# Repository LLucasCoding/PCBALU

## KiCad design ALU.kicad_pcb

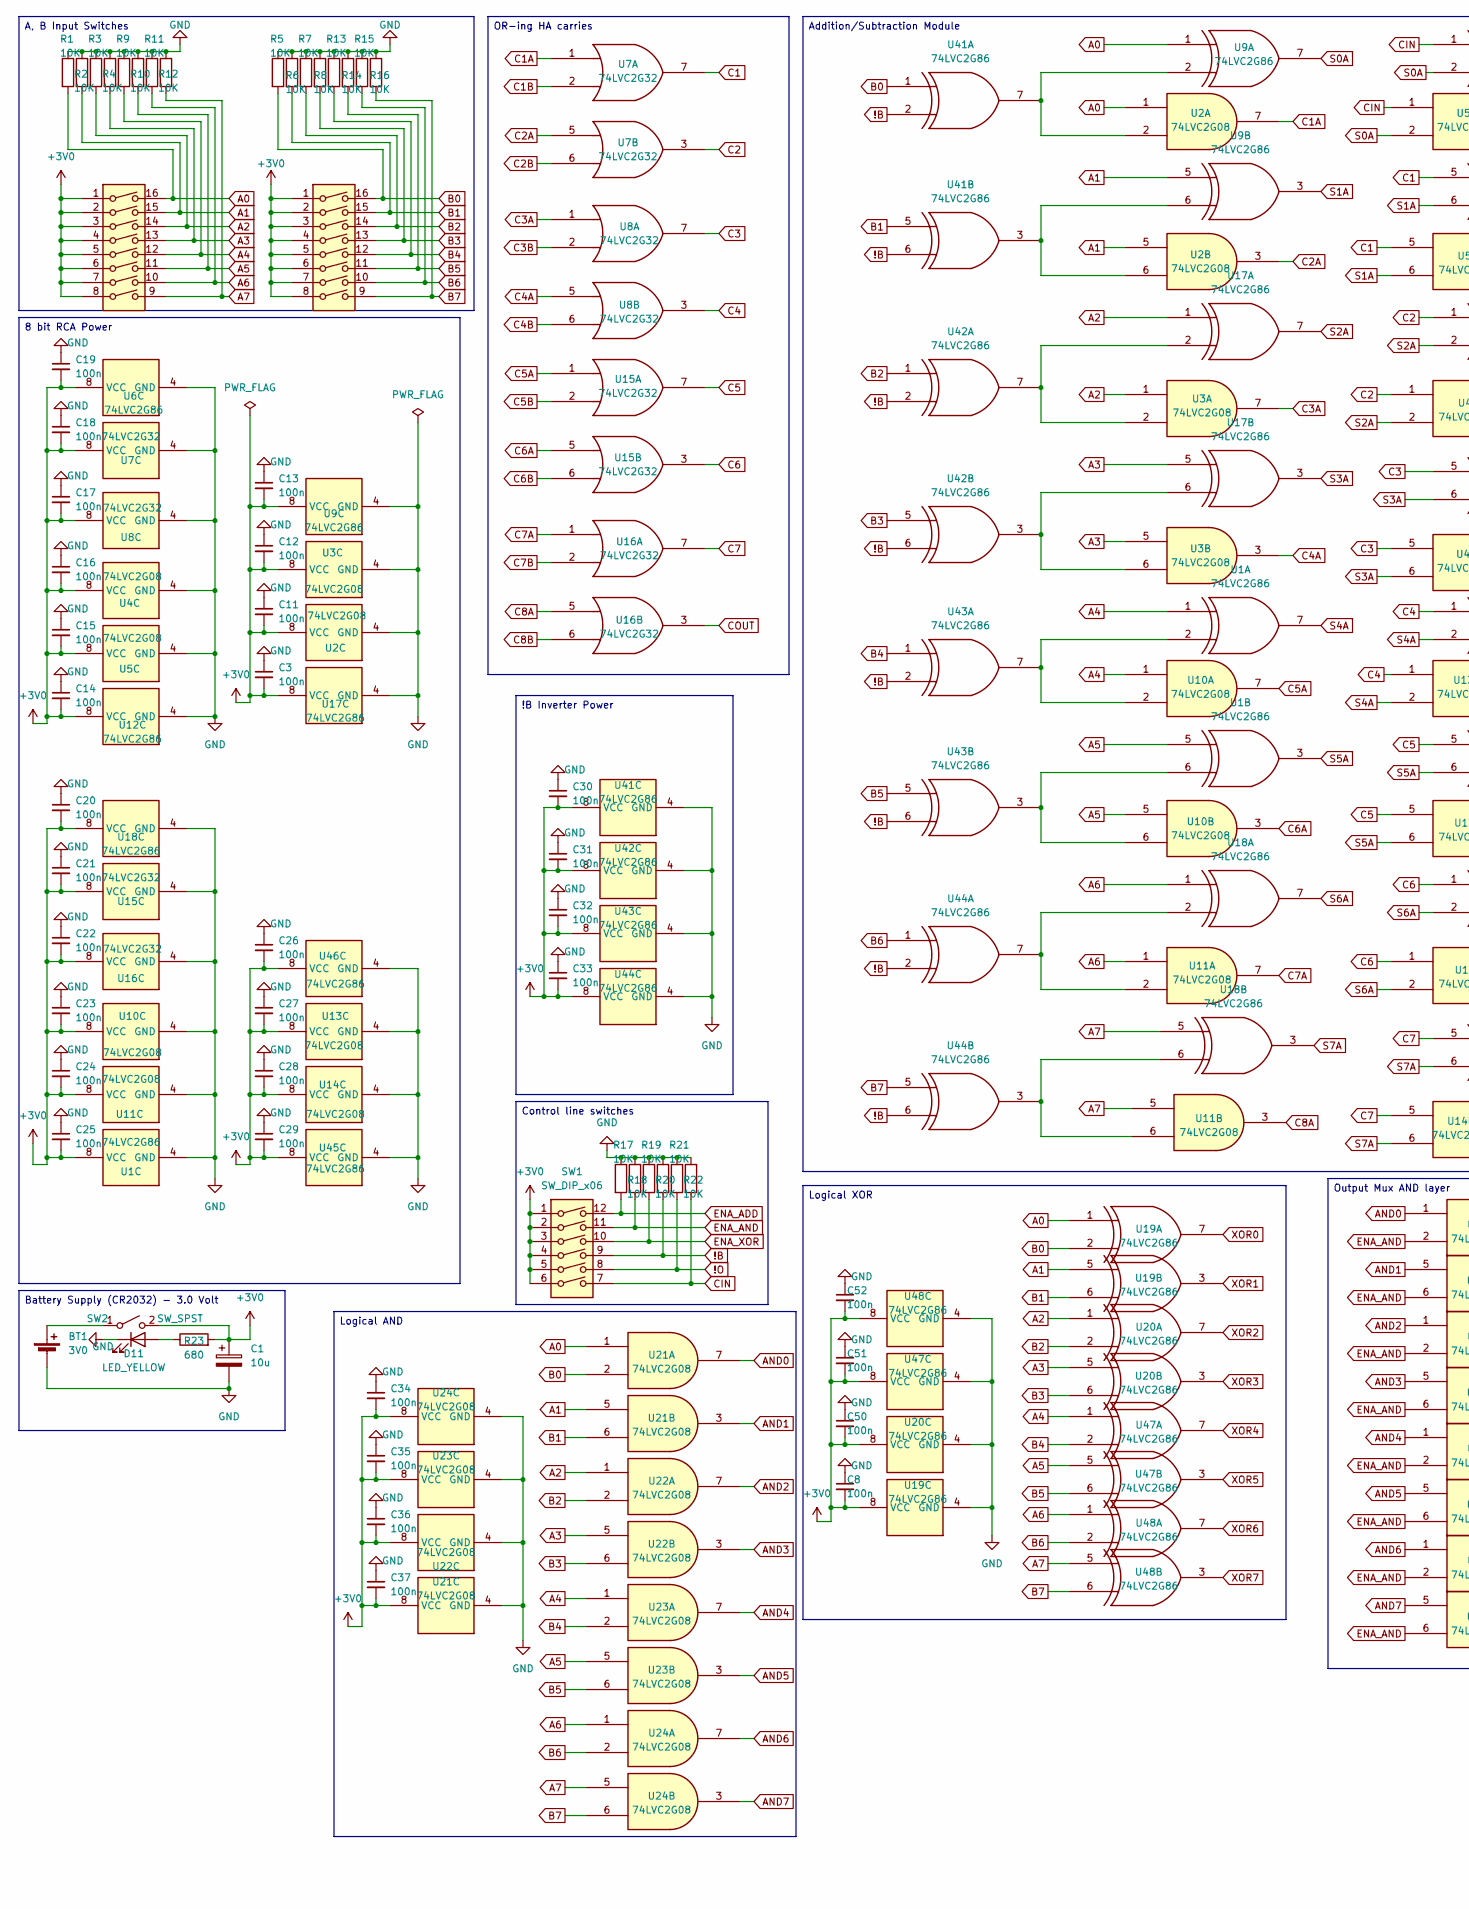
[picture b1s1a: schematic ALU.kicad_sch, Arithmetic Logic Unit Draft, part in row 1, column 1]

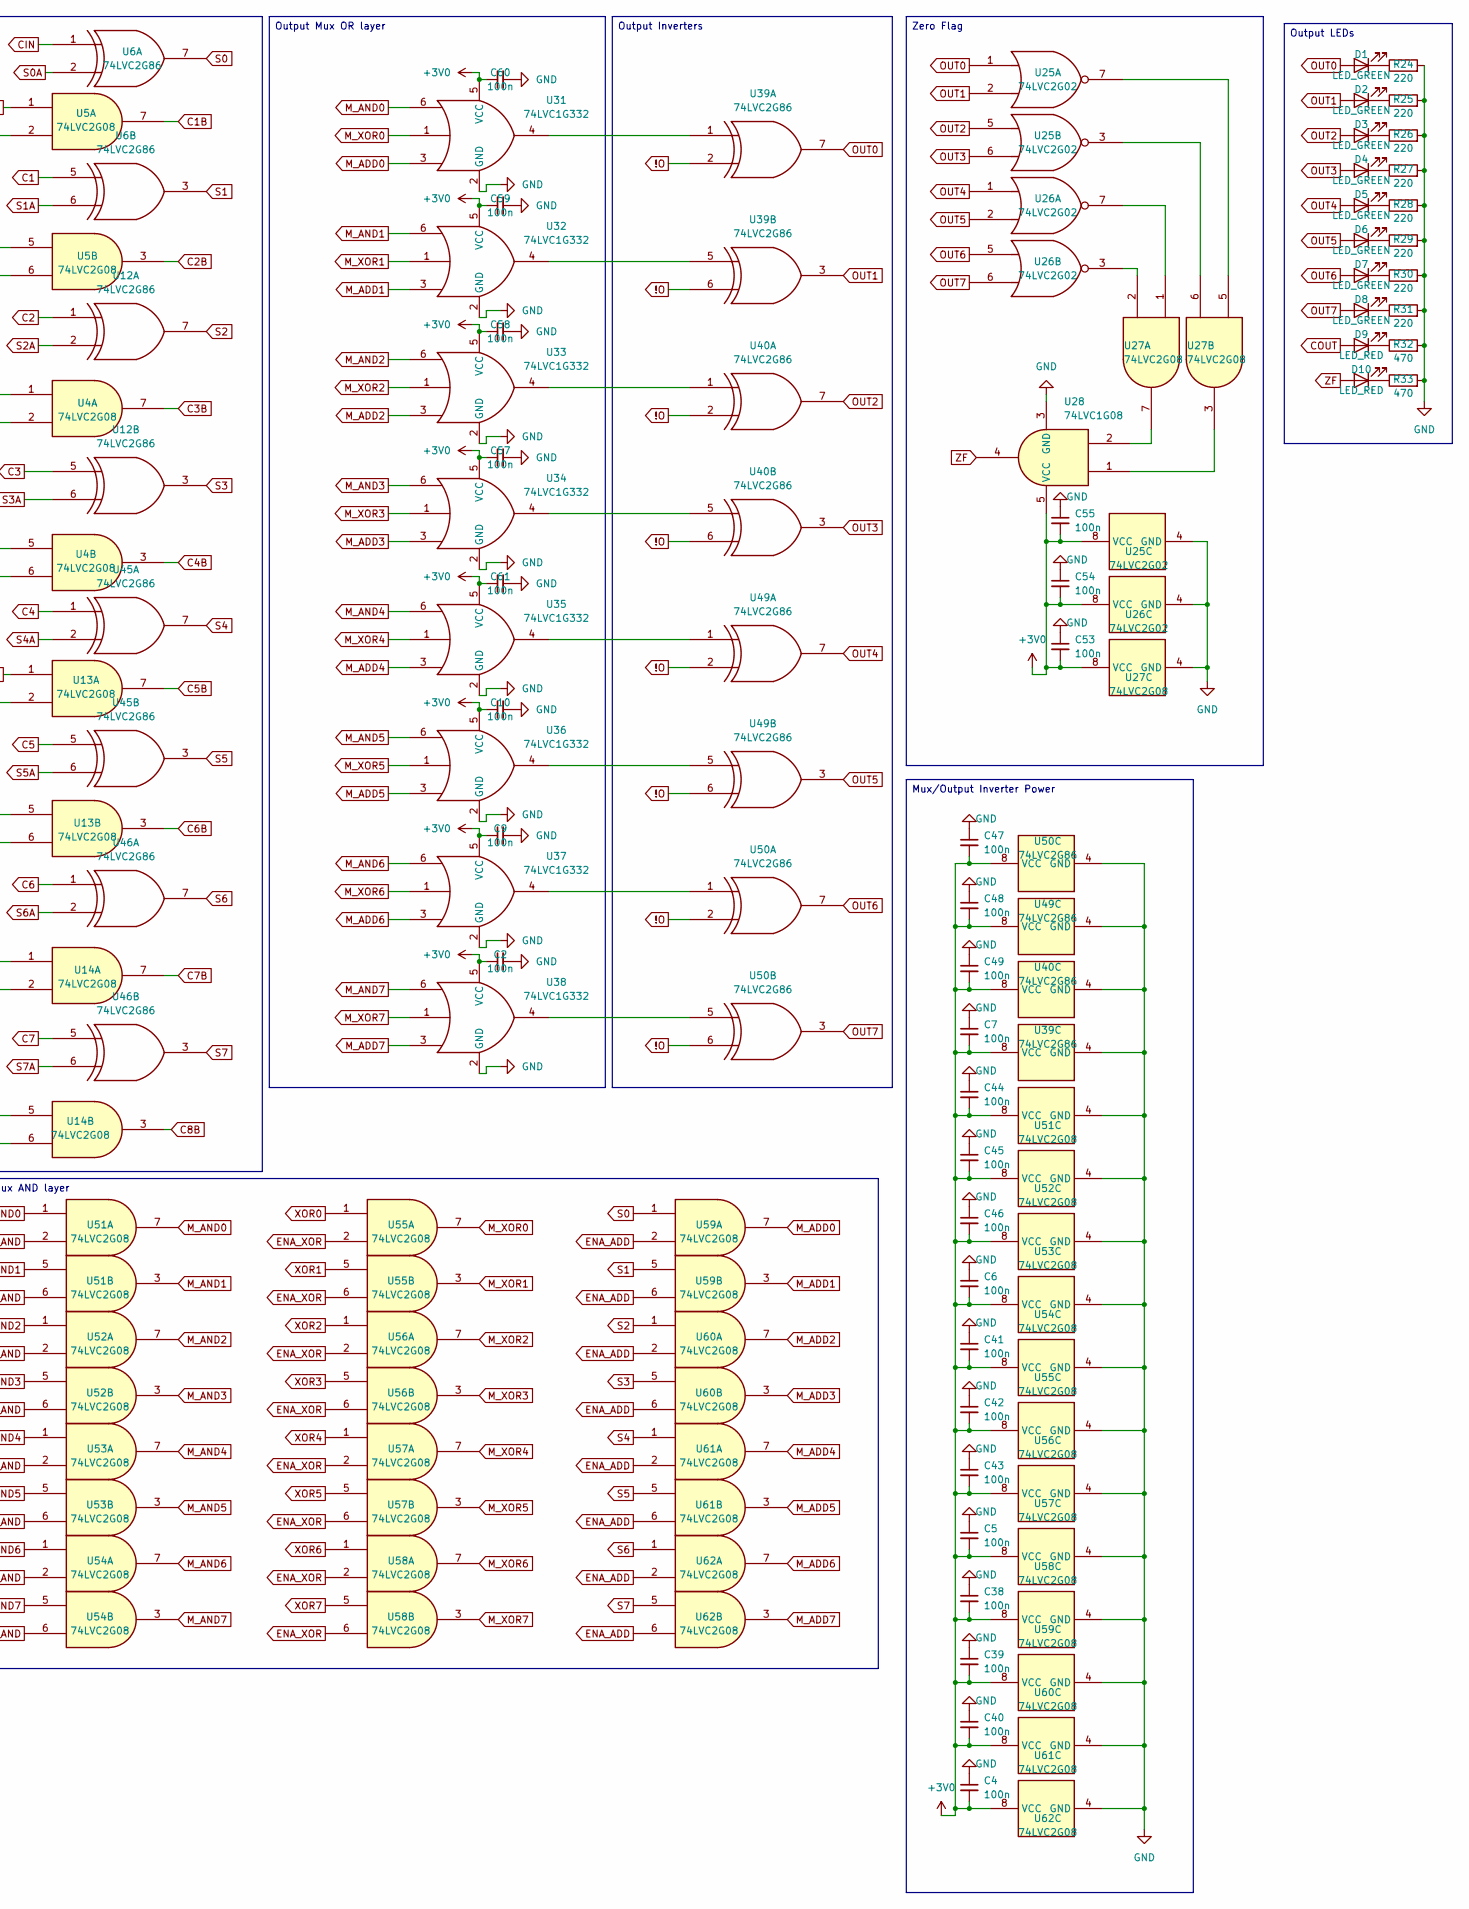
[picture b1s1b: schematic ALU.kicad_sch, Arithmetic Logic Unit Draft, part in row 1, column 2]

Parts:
BT1: 3V0; Battery_Panasonic_CR2032-VS1N_Vertical_CircularHoles
C1: 10u; CP_Radial_D5.0mm_P2.00mm
C2, C3, C4, C5, C6, C7, C8, C9, C10, C11, C12, C13, C14, C15, C16, C17, C18, C19, C20, C21, C22, C23, C24, C25, C26, C27, C28, C29, C30, C31, C32, C33, C34, C35, C36, C37, C38, C39, C40, C41, C42, C43, C44, C45, C46, C47, C48, C49, C50, C51, C52, C53, C54, C55, C57, C58, C59, C60, C61: 100n; C_0805_2012Metric
D1, D2, D3, D4, D5, D6, D7, D8: LED_GREEN; LED_0805_2012Metric
D9, D10: LED_RED; LED_0805_2012Metric
D11: LED_YELLOW; LED_0603_1608Metric
R1, R2, R3, R4, R5, R6, R7, R8, R9, R10, R11, R12, R13, R14, R15, R16, R17, R18, R19, R20, R21, R22: 10K; R_0805_2012Metric
R23: 680; R_0805_2012Metric
R24, R25, R26, R27, R28, R29, R30, R31: 220; R_0805_2012Metric
R32, R33: 470; R_0805_2012Metric
SW1: SW_DIP_x06; SW_DIP_SPSTx06_Slide_9.78x17.42mm_W7.62mm_P2.54mm
SW2: SW_SPST; SW_DIP_SPSTx01_Slide_9.78x4.72mm_W7.62mm_P2.54mm
SW3, SW4: SW_DIP_x08; SW_DIP_SPSTx08_Slide_9.78x22.5mm_W7.62mm_P2.54mm
U1, U6, U9, U12, U17, U18, U19, U20, U39, U40, U41, U42, U43, U44, U45, U46, U47, U48, U49, U50: 74LVC2G86; VSSOP-8_2.3x2mm_P0.5mm
U2, U3, U4, U5, U10, U11, U13, U14, U21, U22, U23, U24, U27, U51, U52, U53, U54, U55, U56, U57, U58, U59, U60, U61, U62: 74LVC2G08; VSSOP-8_2.3x2mm_P0.5mm
U7, U8, U15, U16: 74LVC2G32; VSSOP-8_2.3x2mm_P0.5mm
U25, U26: 74LVC2G02; VSSOP-8_2.3x2mm_P0.5mm
U28: 74LVC1G08; SOT-23-5
U31, U32, U33, U34, U35, U36, U37, U38: 74LVC1G332; SOT-23-6

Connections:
!B: R20.2, SW1.9, U41.2, U41.6, U42.2, U42.6, U43.2, U43.6, U44.2, U44.6
!O: R21.2, SW1.8, U39.2, U39.6, U40.2, U40.6, U49.2, U49.6, U50.2, U50.6
+3V0: C1.1, C2.1, C3.2, C4.2, C5.2, C6.2, C7.2, C8.2, C9.1, C10.1, C11.2, C12.2, C13.2, C14.2, C15.2, C16.2, C17.2, C18.2, C19.2, C20.2, C21.2, C22.2, C23.2, C24.2, C25.2, C26.2, C27.2, C28.2, C29.2, C30.2, C31.2, C32.2, C33.2, C34.2, C35.2, C36.2, C37.2, C38.2, C39.2, C40.2, C41.2, C42.2, C43.2, C44.2, C45.2, C46.2, C47.2, C48.2, C49.2, C50.2, C51.2, C52.2, C53.2, C54.2, C55.2, C57.1, C58.1, C59.1, C60.1, C61.1, R23.2, SW1.1, SW1.2, SW1.3, SW1.4, SW1.5, SW1.6, SW2.2 (B), SW3.1, SW3.2, SW3.3, SW3.4, SW3.5, SW3.6, SW3.7, SW3.8, SW4.1, SW4.2, SW4.3, SW4.4, SW4.5, SW4.6, SW4.7, SW4.8, U1.8 (VCC), U2.8 (VCC), U3.8 (VCC), U4.8 (VCC), U5.8 (VCC), U6.8 (VCC), U7.8 (VCC), U8.8 (VCC), U9.8 (VCC), U10.8 (VCC), U11.8 (VCC), U12.8 (VCC), U13.8 (VCC), U14.8 (VCC), U15.8 (VCC), U16.8 (VCC), U17.8 (VCC), U18.8 (VCC), U19.8 (VCC), U20.8 (VCC), U21.8 (VCC), U22.8 (VCC), U23.8 (VCC), U24.8 (VCC), U25.8 (VCC), U26.8 (VCC), U27.8 (VCC), U28.5 (VCC), U31.5 (VCC), U32.5 (VCC), U33.5 (VCC), U34.5 (VCC), U35.5 (VCC), U36.5 (VCC), U37.5 (VCC), U38.5 (VCC), U39.8 (VCC), U40.8 (VCC), U41.8 (VCC), U42.8 (VCC), U43.8 (VCC), U44.8 (VCC), U45.8 (VCC), U46.8 (VCC), U47.8 (VCC), U48.8 (VCC), U49.8 (VCC), U50.8 (VCC), U51.8 (VCC), U52.8 (VCC), U53.8 (VCC), U54.8 (VCC), U55.8 (VCC), U56.8 (VCC), U57.8 (VCC), U58.8 (VCC), U59.8 (VCC), U60.8 (VCC), U61.8 (VCC), U62.8 (VCC)
A0: R1.2, SW3.16, U2.1, U9.1, U19.1, U21.1
A1: R2.2, SW3.15, U2.5, U9.5, U19.5, U21.5
A2: R3.2, SW3.14, U3.1, U17.1, U20.1, U22.1
A3: R4.2, SW3.13, U3.5, U17.5, U20.5, U22.5
A4: R9.2, SW3.12, U1.1, U10.1, U23.1, U47.1
A5: R10.2, SW3.11, U1.5, U10.5, U23.5, U47.5
A6: R11.2, SW3.10, U11.1, U18.1, U24.1, U48.1
A7: R12.2, SW3.9, U11.5, U18.5, U24.5, U48.5
AND0: U21.7, U51.1
AND1: U21.3, U51.5
AND2: U22.7, U52.1
AND3: U22.3, U52.5
AND4: U23.7, U53.1
AND5: U23.3, U53.5
AND6: U24.7, U54.1
AND7: U24.3, U54.5
B0: R5.2, SW4.16, U19.2, U21.2, U41.1
B1: R6.2, SW4.15, U19.6, U21.6, U41.5
B2: R7.2, SW4.14, U20.2, U22.2, U42.1
B3: R8.2, SW4.13, U20.6, U22.6, U42.5
B4: R13.2, SW4.12, U23.2, U43.1, U47.2
B5: R14.2, SW4.11, U23.6, U43.5, U47.6
B6: R15.2, SW4.10, U24.2, U44.1, U48.2
B7: R16.2, SW4.9, U24.6, U44.5, U48.6
C1: U5.5, U6.5, U7.7
C1A: U2.7, U7.1
C1B: U5.7, U7.2
C2: U4.1, U7.3, U12.1
C2A: U2.3, U7.5
C2B: U5.3, U7.6
C3: U4.5, U8.7, U12.5
C3A: U3.7, U8.1
C3B: U4.7, U8.2
C4: U8.3, U13.1, U45.1
C4A: U3.3, U8.5
C4B: U4.3, U8.6
C5: U13.5, U15.7, U45.5
C5A: U10.7, U15.1
C5B: U13.7, U15.2
C6: U14.1, U15.3, U46.1
C6A: U10.3, U15.5
C6B: U13.3, U15.6
C7: U14.5, U16.7, U46.5
C7A: U11.7, U16.1
C7B: U14.7, U16.2
C8A: U11.3, U16.5
C8B: U14.3, U16.6
CIN: R22.2, SW1.7, U5.1, U6.1
COUT: D9.2 (A), U16.3
ENA_ADD: R17.2, SW1.12, U59.2, U59.6, U60.2, U60.6, U61.2, U61.6, U62.2, U62.6
ENA_AND: R18.2, SW1.11, U51.2, U51.6, U52.2, U52.6, U53.2, U53.6, U54.2, U54.6
ENA_XOR: R19.2, SW1.10, U55.2, U55.6, U56.2, U56.6, U57.2, U57.6, U58.2, U58.6
GND: BT1.2 (-), C1.2, C2.2, C3.1, C4.1, C5.1, C6.1, C7.1, C8.1, C9.2, C10.2, C11.1, C12.1, C13.1, C14.1, C15.1, C16.1, C17.1, C18.1, C19.1, C20.1, C21.1, C22.1, C23.1, C24.1, C25.1, C26.1, C27.1, C28.1, C29.1, C30.1, C31.1, C32.1, C33.1, C34.1, C35.1, C36.1, C37.1, C38.1, C39.1, C40.1, C41.1, C42.1, C43.1, C44.1, C45.1, C46.1, C47.1, C48.1, C49.1, C50.1, C51.1, C52.1, C53.1, C54.1, C55.1, C57.2, C58.2, C59.2, C60.2, C61.2, D11.1 (K), R1.1, R2.1, R3.1, R4.1, R5.1, R6.1, R7.1, R8.1, R9.1, R10.1, R11.1, R12.1, R13.1, R14.1, R15.1, R16.1, R17.1, R18.1, R19.1, R20.1, R21.1, R22.1, R24.2, R25.2, R26.2, R27.2, R28.2, R29.2, R30.2, R31.2, R32.2, R33.2, U1.4 (GND), U2.4 (GND), U3.4 (GND), U4.4 (GND), U5.4 (GND), U6.4 (GND), U7.4 (GND), U8.4 (GND), U9.4 (GND), U10.4 (GND), U11.4 (GND), U12.4 (GND), U13.4 (GND), U14.4 (GND), U15.4 (GND), U16.4 (GND), U17.4 (GND), U18.4 (GND), U19.4 (GND), U20.4 (GND), U21.4 (GND), U22.4 (GND), U23.4 (GND), U24.4 (GND), U25.4 (GND), U26.4 (GND), U27.4 (GND), U28.3 (GND), U31.2 (GND), U32.2 (GND), U33.2 (GND), U34.2 (GND), U35.2 (GND), U36.2 (GND), U37.2 (GND), U38.2 (GND), U39.4 (GND), U40.4 (GND), U41.4 (GND), U42.4 (GND), U43.4 (GND), U44.4 (GND), U45.4 (GND), U46.4 (GND), U47.4 (GND), U48.4 (GND), U49.4 (GND), U50.4 (GND), U51.4 (GND), U52.4 (GND), U53.4 (GND), U54.4 (GND), U55.4 (GND), U56.4 (GND), U57.4 (GND), U58.4 (GND), U59.4 (GND), U60.4 (GND), U61.4 (GND), U62.4 (GND)
M_ADD0: U31.3, U59.7
M_ADD1: U32.3, U59.3
M_ADD2: U33.3, U60.7
M_ADD3: U34.3, U60.3
M_ADD4: U35.3, U61.7
M_ADD5: U36.3, U61.3
M_ADD6: U37.3, U62.7
M_ADD7: U38.3, U62.3
M_AND0: U31.6, U51.7
M_AND1: U32.6, U51.3
M_AND2: U33.6, U52.7
M_AND3: U34.6, U52.3
M_AND4: U35.6, U53.7
M_AND5: U36.6, U53.3
M_AND6: U37.6, U54.7
M_AND7: U38.6, U54.3
M_XOR0: U31.1, U55.7
M_XOR1: U32.1, U55.3
M_XOR2: U33.1, U56.7
M_XOR3: U34.1, U56.3
M_XOR4: U35.1, U57.7
M_XOR5: U36.1, U57.3
M_XOR6: U37.1, U58.7
M_XOR7: U38.1, U58.3
unnamed: BT1.1 (+), SW2.1 (A)
unnamed: D1.1 (K), R24.1
unnamed: D2.1 (K), R25.1
unnamed: D3.1 (K), R26.1
unnamed: D4.1 (K), R27.1
unnamed: D5.1 (K), R28.1
unnamed: D6.1 (K), R29.1
unnamed: D7.1 (K), R30.1
unnamed: D8.1 (K), R31.1
unnamed: D9.1 (K), R32.1
unnamed: D10.1 (K), R33.1
unnamed: D11.2 (A), R23.1
unnamed: U1.2, U10.2, U43.7
unnamed: U1.6, U10.6, U43.3
unnamed: U2.2, U9.2, U41.7
unnamed: U2.6, U9.6, U41.3
unnamed: U11.2, U18.2, U44.7
unnamed: U11.6, U18.6, U44.3
unnamed: U3.2, U17.2, U42.7
unnamed: U3.6, U17.6, U42.3
unnamed: U25.3, U27.6
unnamed: U25.7, U27.5
unnamed: U26.3, U27.2
unnamed: U26.7, U27.1
unnamed: U27.3, U28.1
unnamed: U27.7, U28.2
unnamed: U31.4, U39.1
unnamed: U32.4, U39.5
unnamed: U33.4, U40.1
unnamed: U34.4, U40.5
unnamed: U35.4, U49.1
unnamed: U36.4, U49.5
unnamed: U37.4, U50.1
unnamed: U38.4, U50.5
OUT0: D1.2 (A), U25.1, U39.7
OUT1: D2.2 (A), U25.2, U39.3
OUT2: D3.2 (A), U25.5, U40.7
OUT3: D4.2 (A), U25.6, U40.3
OUT4: D5.2 (A), U26.1, U49.7
OUT5: D6.2 (A), U26.2, U49.3
OUT6: D7.2 (A), U26.5, U50.7
OUT7: D8.2 (A), U26.6, U50.3
S0: U6.7, U59.1
S0A: U5.2, U6.2, U9.7
S1: U6.3, U59.5
S1A: U5.6, U6.6, U9.3
S2: U12.7, U60.1
S2A: U4.2, U12.2, U17.7
S3: U12.3, U60.5
S3A: U4.6, U12.6, U17.3
S4: U45.7, U61.1
S4A: U1.7, U13.2, U45.2
S5: U45.3, U61.5
S5A: U1.3, U13.6, U45.6
S6: U46.7, U62.1
S6A: U14.2, U18.7, U46.2
S7: U46.3, U62.5
S7A: U14.6, U18.3, U46.6
XOR0: U19.7, U55.1
XOR1: U19.3, U55.5
XOR2: U20.7, U56.1
XOR3: U20.3, U56.5
XOR4: U47.7, U57.1
XOR5: U47.3, U57.5
XOR6: U48.7, U58.1
XOR7: U48.3, U58.5
ZF: D10.2 (A), U28.4

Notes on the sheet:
Mux/Output Inverter Power
Battery Supply (CR2032) - 3.0 Volt
OR-ing HA carries
Output Inverters
Output Mux OR layer
Control line switches
Logical AND
Zero Flag
Logical XOR
8 bit RCA Power
Addition/Subtraction Module
A, B Input Switches
Output LEDs
Output Mux AND layer
!B Inverter Power

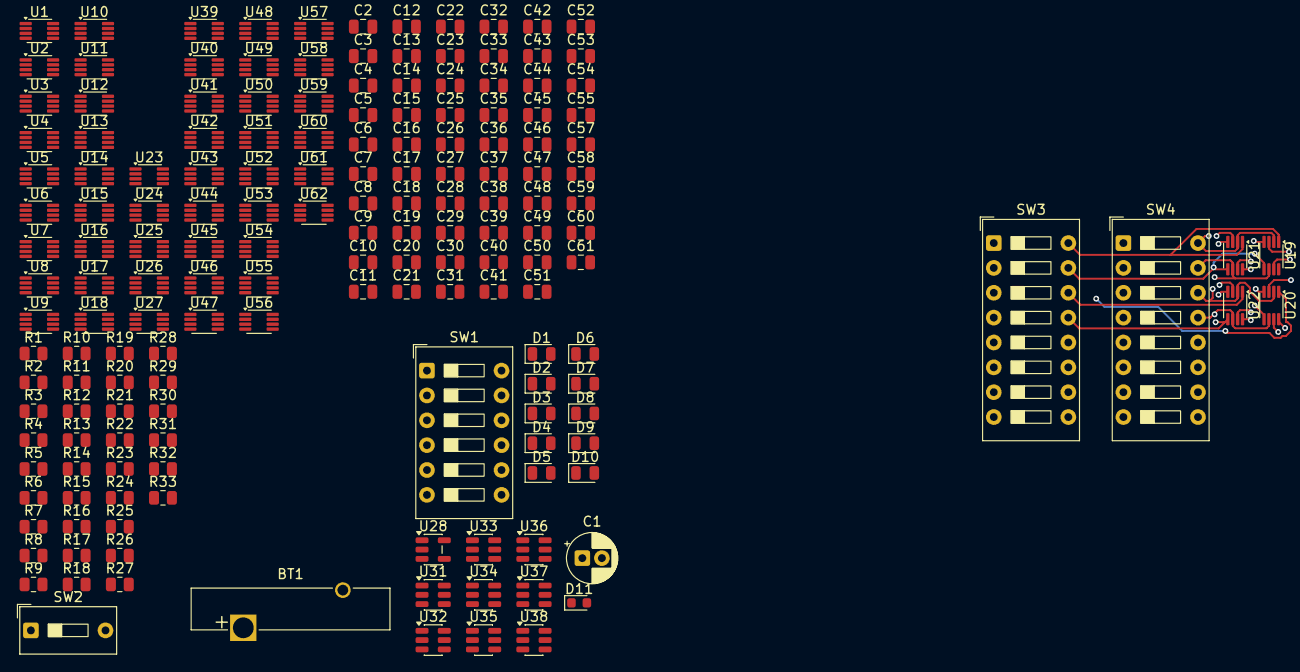
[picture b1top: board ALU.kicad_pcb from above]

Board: 2 copper layers, 169 parts (0 on the bottom side), 147 nets.

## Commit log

2026-05-08 Me when I actually upload the files
    mmmm tasty
2026-05-08 Subtraction and logical operations
    hmmm yes tasty
    Total work time: 5.5 hours
2026-05-08 mux and stuff
    6.6 hours work time
2026-05-08 Revision 1.0!
    9.2 hours work time
2026-05-09 Revision 2.0 - Decoupling capacitors + Footprints
    11.1 hours work time
2026-05-11 pcb layout start (attempt 3)
    15.3 hours work time
